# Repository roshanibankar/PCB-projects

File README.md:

## Circuits
* LED (Getting started with KiCAD basics essential guide)

* Google Dino Game Player using LDR sensors (dinorun4)

* Ultrasonic sensor distance and depth determination with Arduino(Depth)

* LED Heart Blinker (A heart-shaped PCB powered by a **555 Timer** in astable mode. Features 14 LEDs that create a pulsing heartbeat effect.)
**Design:** Created in KiCad.
**Power:** 9V Battery.
**Manufacture:** Upload `valentine's-heart-pcb.zip` to any PCB fabricator.

* audio-sync-led // Beat‑Triggered LED Bracelet for concerts

* Real mini photobooth you can build into a case.

* A little robot that follows light or avoids darkness.

* A compact, single ESP32 sensor board that can stand alone.

* A small, self-contained “smart button board” for experiments or IoT control.

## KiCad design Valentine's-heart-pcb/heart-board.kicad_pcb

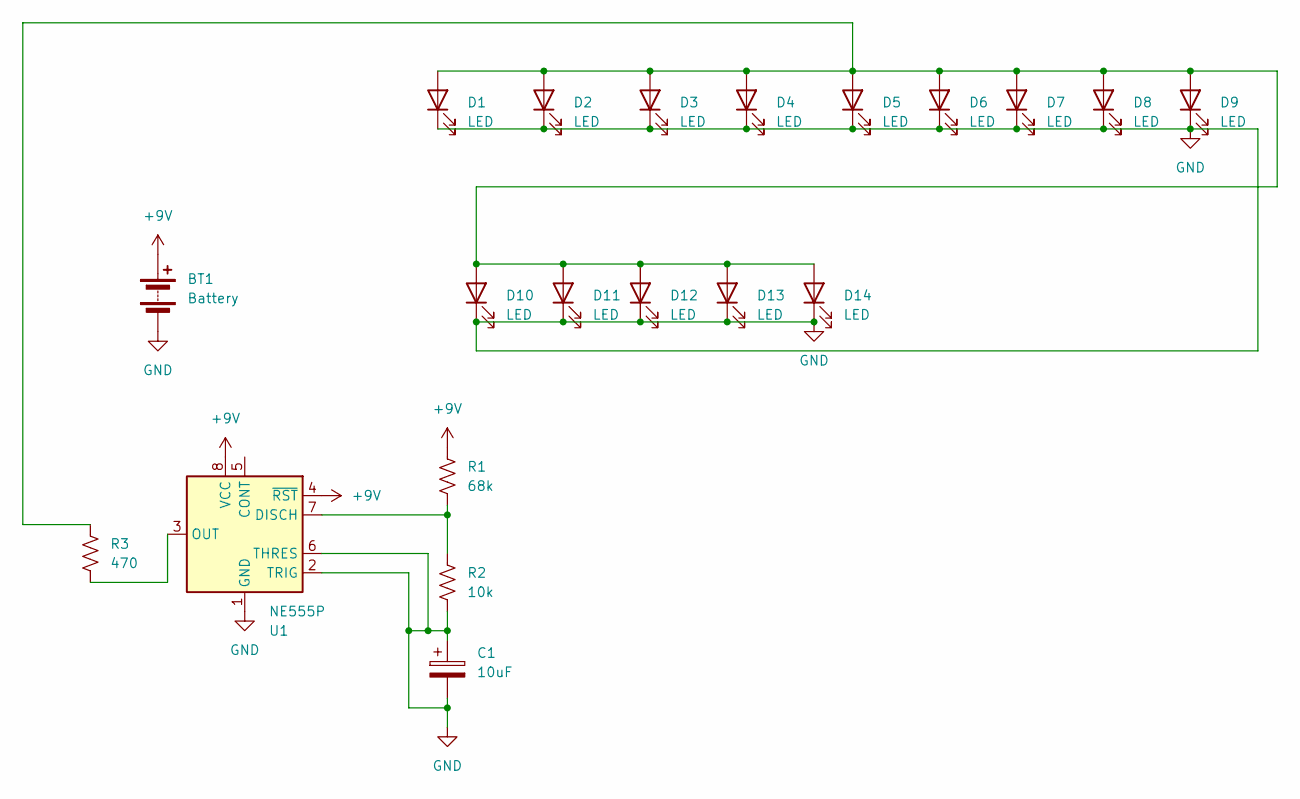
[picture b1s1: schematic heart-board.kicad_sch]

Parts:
BT1: Battery; PinHeader_1x02_P2.54mm_Vertical
C1: 10uF; CP_Radial_D5.0mm_P2.00mm
D1, D2, D3, D4, D5, D6, D7, D8, D9, D10, D11, D12, D13, D14: LED; LED_D5.0mm
R1: 68k; R_Axial_DIN0207_L6.3mm_D2.5mm_P7.62mm_Horizontal
R2: 10k; R_Axial_DIN0207_L6.3mm_D2.5mm_P7.62mm_Horizontal
R3: 470; R_Axial_DIN0207_L6.3mm_D2.5mm_P7.62mm_Horizontal
U1: NE555P; DIP-8_W7.62mm

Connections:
+9V: BT1.1 (+), R1.1, U1.4 (~RST), U1.8 (VCC)
GND: BT1.2 (-), C1.1, C1.2, D1.1 (K), D2.1 (K), D3.1 (K), D4.1 (K), D5.1 (K), D6.1 (K), D7.1 (K), D8.1 (K), D9.1 (K), D10.1 (K), D11.1 (K), D12.1 (K), D13.1 (K), D14.1 (K), R2.2, U1.1 (GND), U1.2 (TRIG), U1.6 (THRES)
unnamed: D1.2 (A), D2.2 (A), D3.2 (A), D4.2 (A), D5.2 (A), D6.2 (A), D7.2 (A), D8.2 (A), D9.2 (A), D10.2 (A), D11.2 (A), D12.2 (A), D13.2 (A), D14.2 (A), R3.1
unnamed: R1.2, R2.1, U1.7 (DISCH)
unnamed: R3.2, U1.3 (OUT)

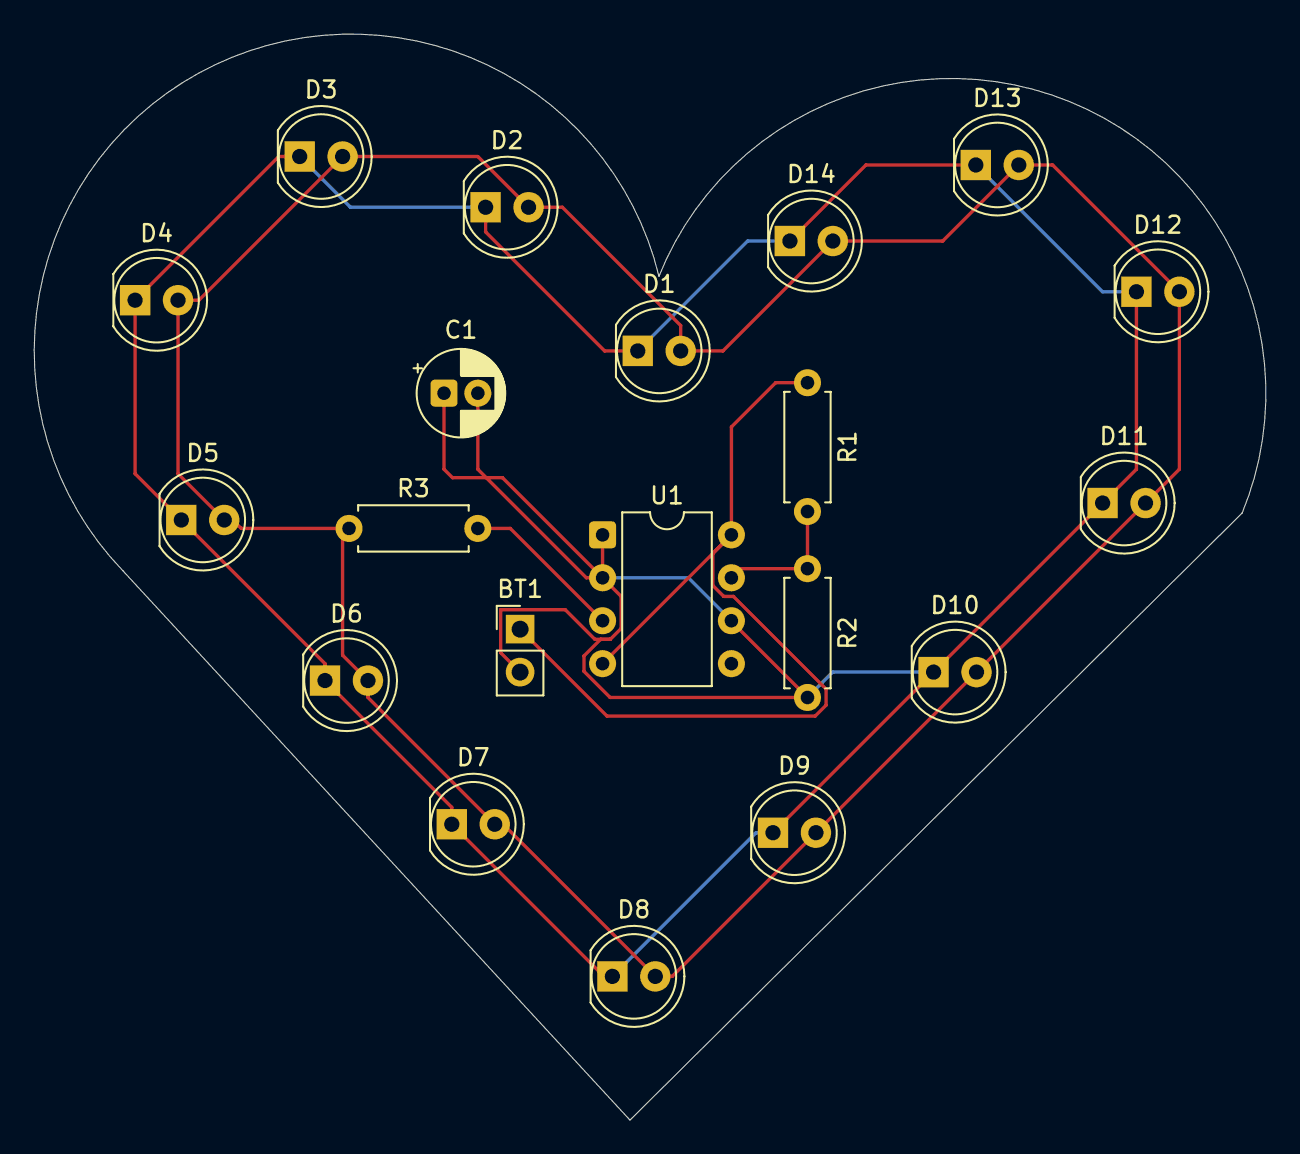
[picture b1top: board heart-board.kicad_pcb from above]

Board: 2 copper layers, 72.9 x 64.2 mm, 20 parts (0 on the bottom side), 5 nets.

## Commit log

2026-02-08 Dino Run
2026-02-11 Depth with ultrasonic
2026-02-13 Add LED guide to Arduino section in README
2026-02-20 Valentine's PCB board
2026-02-20 Update README to remove materials list
    Removed materials list for LED Heart Blinker project.
2026-02-20 schematic images
